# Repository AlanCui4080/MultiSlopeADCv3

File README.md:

# MultiSlopeADCv3
a multislope adc with only runup, i knew there are typos in my file :(

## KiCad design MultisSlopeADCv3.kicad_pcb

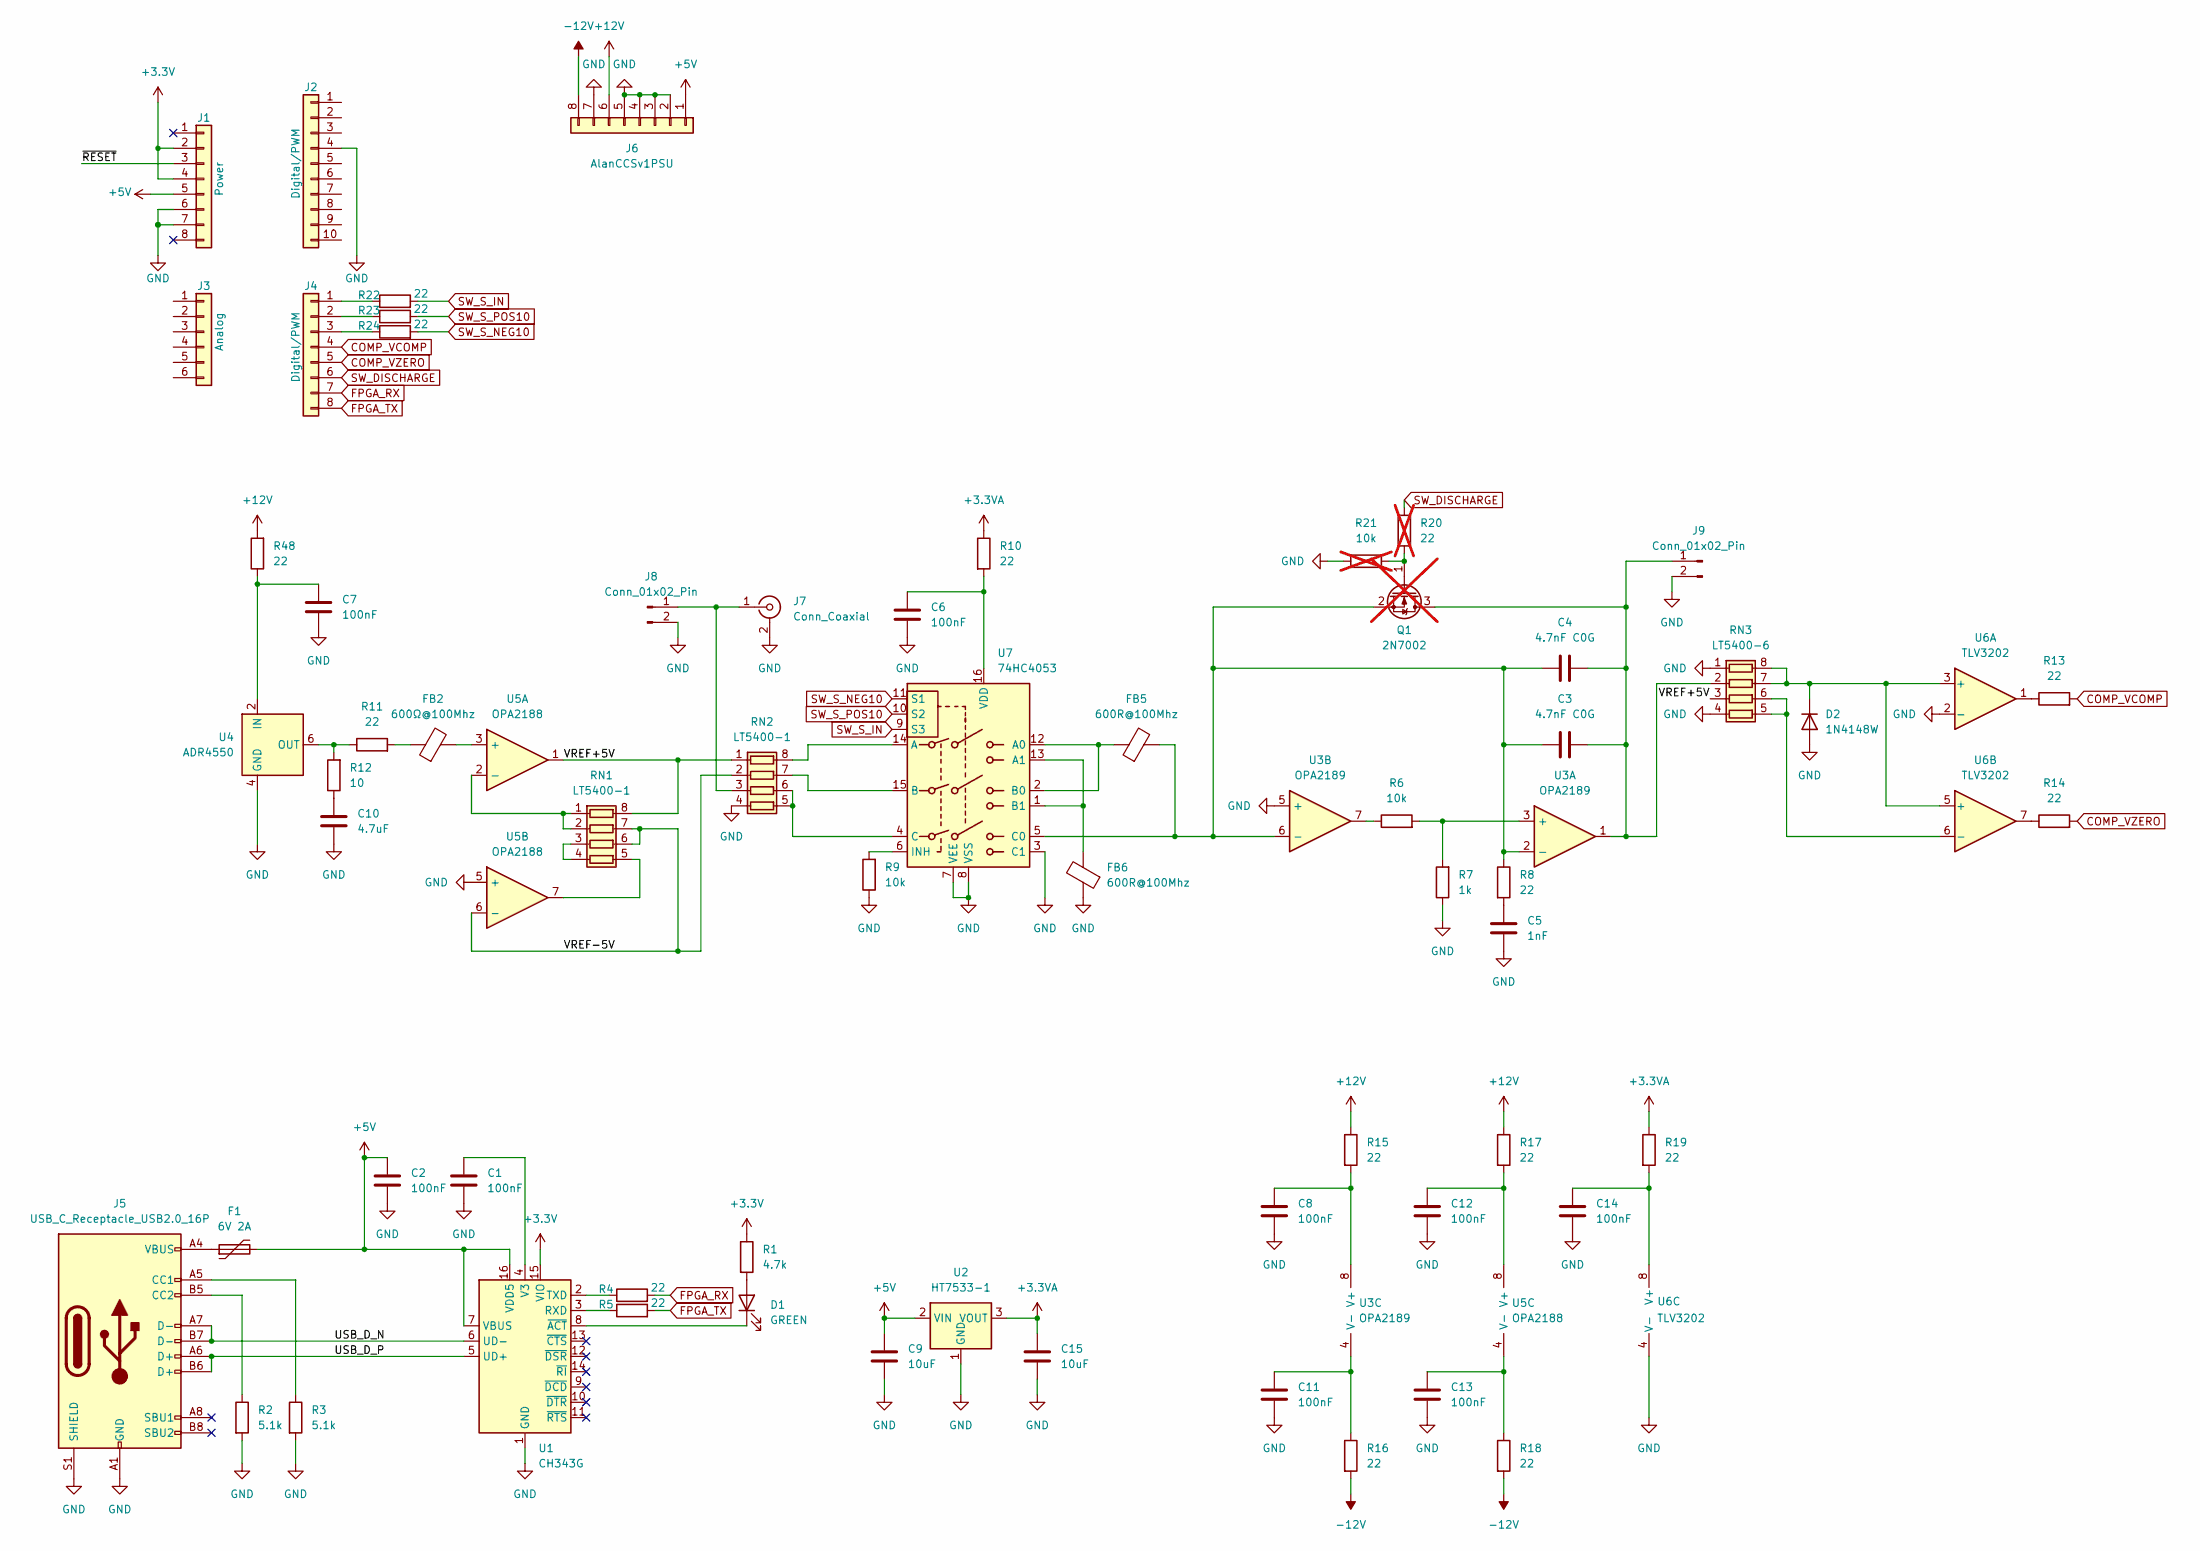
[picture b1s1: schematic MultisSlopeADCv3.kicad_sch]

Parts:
C1, C2, C6, C7, C8, C11, C12, C13, C14: 100nF; C_0603_1608Metric
C3, C4: 4.7nF C0G; C_1206_3216Metric
C5: 1nF; C_0603_1608Metric
C9, C15: 10uF; C_0805_2012Metric
C10: 4.7uF; C_0603_1608Metric
D1: GREEN; LED_0603_1608Metric
D2: 1N4148W; D_SOD-123
F1: 6V 2A; Fuse_1206_3216Metric
FB2: 600Ω@100Mhz; L_0603_1608Metric
FB5, FB6: 600R@100Mhz; L_0603_1608Metric
J1: Power; PinSocket_1x08_P2.54mm_Vertical
J2: Digital/PWM; PinSocket_1x10_P2.54mm_Vertical
J3: Analog; PinSocket_1x06_P2.54mm_Vertical
J4: Digital/PWM; PinSocket_1x08_P2.54mm_Vertical
J5: USB_C_Receptacle_USB2.0_16P; USB_C_Receptacle_GCT_USB4105-xx-A_16P_TopMnt_Horizontal
J6: AlanCCSv1PSU; PinSocket_1x08_P2.54mm_Vertical
J7: Conn_Coaxial; SMA_Amphenol_901-144_Vertical
J8, J9: Conn_01x02_Pin; PinHeader_1x02_P2.54mm_Vertical
Q1: 2N7002; SOT-23; not fitted
R1: 4.7k; R_0603_1608Metric
R2, R3: 5.1k; R_0603_1608Metric
R4, R5, R8, R10, R11, R13, R14, R15, R16, R17, R18, R19, R22, R23, R24, R48: 22; R_0603_1608Metric
R6, R9: 10k; R_0603_1608Metric
R7: 1k; R_0603_1608Metric
R12: 10; R_0603_1608Metric
R20: 22; R_0603_1608Metric; not fitted
R21: 10k; R_0603_1608Metric; not fitted
RN1, RN2: LT5400-1; MSOP-8_3x3mm_P0.65mm
RN3: LT5400-6; MSOP-8_3x3mm_P0.65mm
U1: CH343G; SOIC-16_3.9x9.9mm_P1.27mm
U2: HT7533-1; SOT-89-3
U3: OPA2189; SOIC-8_3.9x4.9mm_P1.27mm
U4: ADR4550; SOIC-8_3.9x4.9mm_P1.27mm
U5: OPA2188; SOIC-8_3.9x4.9mm_P1.27mm
U6: TLV3202; SOIC-8_3.9x4.9mm_P1.27mm
U7: 74HC4053; SOIC-16_3.9x9.9mm_P1.27mm

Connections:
+3.3V: J1.2, J1.4, R1.1, U1.15 (VIO)
+3.3VA: C15.1, R10.1, R19.1, U2.3 (VOUT)
+5V: C2.1, C9.1, F1.2, J1.5, J6.1, U1.7 (VBUS), U1.16 (VDD5), U2.2 (VIN)
+12V: J6.6, R15.1, R17.1, R48.2
-12V: J6.8, R16.2, R18.2
/USB_D_N: J5.A7 (D-), J5.B7 (D-), U1.6 (UD-)
/USB_D_P: J5.A6 (D+), J5.B6 (D+), U1.5 (UD+)
/VREF+5V: RN1.8 (R1.2), RN2.1 (R1.1), RN3.3 (R3.1), U5.1
/VREF-5V: RN1.6 (R3.2), RN1.7 (R2.2), RN2.2 (R2.1), U5.6 (-)
/~RESET: J1.3
COMP_VCOMP: J4.4, R13.2
COMP_VZERO: J4.5, R14.2
FPGA_RX: J4.7, R4.2
FPGA_TX: J4.8, R5.2
GND: C1.2, C2.2, C5.2, C6.2, C7.1, C8.2, C9.2, C10.1, C11.2, C12.2, C13.2, C14.2, C15.2, D2.2 (A), FB6.1, J1.6, J1.7, J2.4, J5.A1 (GND), J5.A12 (GND), J5.B1 (GND), J5.B12 (GND), J5.S1 (SHIELD), J6.2, J6.3, J6.4, J6.5, J6.7, J7.2 (Ext), J8.2, J9.2, R2.2, R3.2, R7.1, R9.1, R21.2, RN2.4 (R4.1), RN3.1 (R1.1), RN3.4 (R4.1), U1.1 (GND), U2.1 (GND), U3.5 (+), U4.4 (GND), U5.5 (+), U6.2 (-), U6.4 (V-), U7.3 (C1), U7.7 (VEE), U7.8 (VSS)
unnamed: C5.1, R8.2
unnamed: C10.2, R12.1
unnamed: D1.2 (A), R1.2
unnamed: D1.1 (K), U1.8 (~ACT)
unnamed: D2.1 (K), RN3.7 (R2.2), RN3.8 (R1.2), U6.3 (+), U6.5 (+)
unnamed: F1.1, J5.A4 (VBUS), J5.A9 (VBUS), J5.B4 (VBUS), J5.B9 (VBUS)
unnamed: FB2.1, R11.2
unnamed: J4.1, R22.1
unnamed: J4.2, R23.1
unnamed: J4.3, R24.1
unnamed: J5.A5 (CC1), R3.1
unnamed: J5.B5 (CC2), R2.1
unnamed: J7.1 (In), J8.1, RN2.3 (R3.1)
unnamed: C3.2, C4.2, J9.1, Q1.3 (D), RN3.2 (R2.1), U3.1
unnamed: Q1.1 (G), R20.2, R21.1
unnamed: C3.1, C4.1, FB5.2, Q1.2 (S), R8.1, U3.2 (-), U3.6 (-), U7.5 (C0)
unnamed: R6.1, U3.7
unnamed: R13.1, U6.1
unnamed: R14.1, U6.7
unnamed: RN1.1 (R1.1), RN1.2 (R2.1), U5.2 (-)
unnamed: RN1.3 (R3.1), RN1.4 (R4.1)
unnamed: RN1.5 (R4.2), U5.7
unnamed: RN2.8 (R1.2), U7.14 (A)
unnamed: RN2.7 (R2.2), U7.15 (B)
unnamed: RN2.5 (R4.2), RN2.6 (R3.2), U7.4 (C)
unnamed: RN3.5 (R4.2), RN3.6 (R3.2), U6.6 (-)
unnamed: R5.1, U1.3 (RXD)
unnamed: R4.1, U1.2 (TXD)
unnamed: C1.1, U1.4 (V3)
unnamed: R6.2, R7.2, U3.3 (+)
unnamed: C8.1, R15.2, U3.8 (V+)
unnamed: C11.1, R16.1, U3.4 (V-)
unnamed: C7.2, R48.1, U4.2 (IN)
unnamed: R11.1, R12.2, U4.6 (OUT)
unnamed: FB2.2, U5.3 (+)
unnamed: C12.1, R17.2, U5.8 (V+)
unnamed: C13.1, R18.1, U5.4 (V-)
unnamed: C14.1, R19.2, U6.8 (V+)
unnamed: FB5.1, U7.2 (B0), U7.12 (A0)
unnamed: FB6.2, U7.1 (B1), U7.13 (A1)
unnamed: R9.2, U7.6 (INH)
unnamed: C6.1, R10.2, U7.16 (VDD)
SW_DISCHARGE: J4.6, R20.1
SW_S_IN: R22.2, U7.9 (S3)
SW_S_NEG10: R24.2, U7.11 (S1)
SW_S_POS10: R23.2, U7.10 (S2)

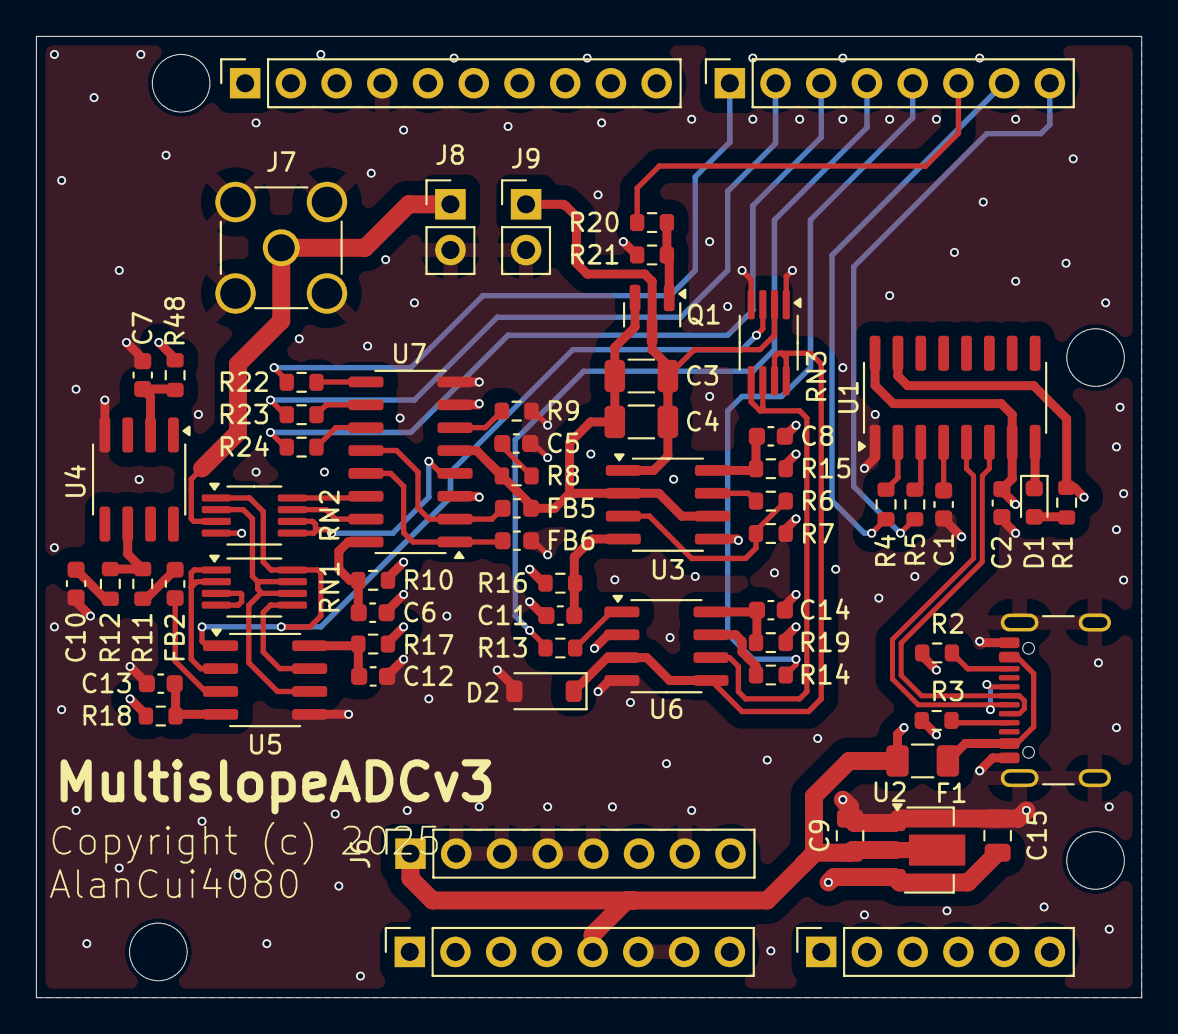
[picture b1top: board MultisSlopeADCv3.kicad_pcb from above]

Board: 4 copper layers, 61.4 x 53.4 mm, 70 parts (0 on the bottom side), 60 nets.

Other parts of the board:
MH1, MH2, MH3, MH4: MountingHole_3.2mm

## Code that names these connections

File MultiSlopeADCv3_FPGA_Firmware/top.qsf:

# -------------------------------------------------------------------------- #
#
# Copyright (C) 2024  Intel Corporation. All rights reserved.
# Your use of Intel Corporation's design tools, logic functions 
# and other software and tools, and any partner logic 
# functions, and any output files from any of the foregoing 
# (including device programming or simulation files), and any 
# associated documentation or information are expressly subject 
# to the terms and conditions of the Intel Program License 
# Subscription Agreement, the Intel Quartus Prime License Agreement,
# the Intel FPGA IP License Agreement, or other applicable license
# agreement, including, without limitation, that your use is for
# the sole purpose of programming logic devices manufactured by
# Intel and sold by Intel or its authorized distributors.  Please
# refer to the applicable agreement for further details, at
# https://fpgasoftware.intel.com/eula.
#
# -------------------------------------------------------------------------- #
#
# Quartus Prime
# Version 23.1std.1 Build 993 05/14/2024 SC Lite Edition
# Date created = 13:40:14  April 21, 2025
#
# -------------------------------------------------------------------------- #
#
# Notes:
#
# 1) The default values for assignments are stored in the file:
#		top_assignment_defaults.qdf
#    If this file doesn't exist, see file:
#		assignment_defaults.qdf
#
# 2) Intel recommends that you do not modify this file. This
#    file is updated automatically by the Quartus Prime software
#    and any changes you make may be lost or overwritten.
#
# -------------------------------------------------------------------------- #


set_global_assignment -name FAMILY "MAX 10"
set_global_assignment -name DEVICE 10M08SAE144C8G
set_global_assignment -name TOP_LEVEL_ENTITY top
set_global_assignment -name ORIGINAL_QUARTUS_VERSION 23.1STD.1
set_global_assignment -name PROJECT_CREATION_TIME_DATE "13:40:14  APRIL 21, 2025"
set_global_assignment -name LAST_QUARTUS_VERSION "23.1std.1 Lite Edition"
set_global_assignment -name PROJECT_OUTPUT_DIRECTORY output_files
set_global_assignment -name MIN_CORE_JUNCTION_TEMP 0
set_global_assignment -name MAX_CORE_JUNCTION_TEMP 85
set_global_assignment -name ERROR_CHECK_FREQUENCY_DIVISOR 256
set_global_assignment -name EDA_DESIGN_ENTRY_SYNTHESIS_TOOL "Synplify Pro"
set_global_assignment -name EDA_LMF_FILE synplcty.lmf -section_id eda_design_synthesis
set_global_assignment -name EDA_INPUT_DATA_FORMAT VQM -section_id eda_design_synthesis
set_global_assignment -name EDA_SIMULATION_TOOL "Questa Intel FPGA (Verilog)"
set_global_assignment -name EDA_TIME_SCALE "1 ps" -section_id eda_simulation
set_global_assignment -name EDA_OUTPUT_DATA_FORMAT "VERILOG HDL" -section_id eda_simulation
set_global_assignment -name EDA_GENERATE_FUNCTIONAL_NETLIST OFF -section_id eda_board_design_timing
set_global_assignment -name EDA_GENERATE_FUNCTIONAL_NETLIST OFF -section_id eda_board_design_symbol
set_global_assignment -name EDA_GENERATE_FUNCTIONAL_NETLIST OFF -section_id eda_board_design_signal_integrity
set_global_assignment -name EDA_GENERATE_FUNCTIONAL_NETLIST OFF -section_id eda_board_design_boundary_scan
set_global_assignment -name PARTITION_NETLIST_TYPE SOURCE -section_id Top
set_global_assignment -name PARTITION_FITTER_PRESERVATION_LEVEL PLACEMENT_AND_ROUTING -section_id Top
set_global_assignment -name PARTITION_COLOR 16764057 -section_id Top
set_instance_assignment -name IO_STANDARD "3.3-V LVTTL" -to clk
set_global_assignment -name ENABLE_OCT_DONE ON
set_global_assignment -name USE_CONFIGURATION_DEVICE ON
set_global_assignment -name CRC_ERROR_OPEN_DRAIN OFF
set_global_assignment -name STRATIX_DEVICE_IO_STANDARD "3.3-V LVTTL"
set_global_assignment -name OUTPUT_IO_TIMING_NEAR_END_VMEAS "HALF VCCIO" -rise
set_global_assignment -name OUTPUT_IO_TIMING_NEAR_END_VMEAS "HALF VCCIO" -fall
set_global_assignment -name OUTPUT_IO_TIMING_FAR_END_VMEAS "HALF SIGNAL SWING" -rise
set_global_assignment -name OUTPUT_IO_TIMING_FAR_END_VMEAS "HALF SIGNAL SWING" -fall
set_location_assignment PIN_86 -to sw_s_in
set_location_assignment PIN_84 -to sw_s_pos10
set_location_assignment PIN_81 -to sw_s_neg10
set_location_assignment PIN_77 -to comp_vcomp
set_location_assignment PIN_79 -to comp_vzero
set_location_assignment PIN_76 -to sw_discharge
set_location_assignment PIN_75 -to uart_rx
set_location_assignment PIN_74 -to uart_tx
set_location_assignment PIN_27 -to clk
set_location_assignment PIN_121 -to reset_n
set_global_assignment -name ENABLE_SIGNALTAP OFF
set_global_assignment -name USE_SIGNALTAP_FILE output_files/stp1.stp
set_global_assignment -name POWER_PRESET_COOLING_SOLUTION "23 MM HEAT SINK WITH 200 LFPM AIRFLOW"
set_global_assignment -name POWER_BOARD_THERMAL_MODEL "NONE (CONSERVATIVE)"
set_global_assignment -name FLOW_ENABLE_POWER_ANALYZER ON
set_global_assignment -name POWER_DEFAULT_INPUT_IO_TOGGLE_RATE "12.5 %"
set_global_assignment -name SDC_FILE top.out.sdc
set_global_assignment -name VERILOG_FILE thcattus_uart_tx.v
set_global_assignment -name VERILOG_FILE top.v
set_global_assignment -name SIGNALTAP_FILE output_files/stp1.stp
set_global_assignment -name SIGNALTAP_FILE stp1.stp
set_global_assignment -name QIP_FILE system_pll.qip
set_global_assignment -name SMART_RECOMPILE OFF
set_global_assignment -name TIMING_ANALYZER_MULTICORNER_ANALYSIS ON
set_global_assignment -name OPTIMIZATION_MODE BALANCED
set_instance_assignment -name PARTITION_HIERARCHY root_partition -to | -section_id Top

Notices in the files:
MultisSlopeADCv3.kicad_pcb:
Copyright (c) 2025
